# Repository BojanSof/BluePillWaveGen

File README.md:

# STM32 BluePill DDS WaveGen

DDS function generator implemented with STM32 BluePill board, based on
STM32F103C8T6 microcontroller, 8-bit R-2R ladder DAC and additional circuitry
for removing the DC offset.

The user interface is realized with OLED display based on SSD1306 controller and
incremental rotary encoder.

## Specs

Goal specs:

- Waveforms: sine, square, triangle, sawtooth (arbitrary waveforms can easily be
  added)
- Frequency: 0 - 35 kHz, frequncy resolution is variable
- Amplitude: 500 - 3000 mV (software control)

Additional tests and modifications should be done to reach the specs.

## Working Principle

The MCU generates the data for the 8-bit R-2R ladder D/A converter.

Two of the op amps inside TL084 are used as voltage buffers, one for the output
of the DAC and the second one for the variable voltage generated by filtering
PWM signal outputed by the MCU.
This variable voltage is used to remove the DC offset of the generated waveform.
Removing the DC offset is realised with the third op amp, which subtracts the
output of the DAC and the variable voltage and multiplies this difference by
1.82 so the output signal has maximum amplitude of 3 V.

To generate the data for the DAC, each waveform has lookup table stored in the
Flash memory of the MCU, with 256 elements with size 1 byte.
The values stored in the table are actually the data that need to be fed into
the DAC.
During runtime, whole or part of the table is copied into SRAM of the MCU, based
on the frequency of the waveform.
By changing the LUT, arbitrary periodic waveforms can be generated.

Timer 2 of the MCU is configured to generate DMA request.
It has base clock of  14.4 MHz and the value stored in the Auto-Reload Register 
(ARR) depends on the  frequency of the waveform. The value for ARR is calculated
using the following formula:

<center>ARR=TIM2\_BaseClock/(L\*f) - 1</center>

where L is the size of the LUT stored in SRAM and f is the frequency of the
waveform.

The DMA unit transfers data from the LUT in SRAM to the GPIOA output data
register.
The pins PA0-PA7 are used to output the data to the DAC.
Because the output data register of GPIOA is used, the pins PA8-PA15 can not be
used as general purpose outputs, but can be used in the other modes.
This problem can be resolved by writing to the bit set reset register instead of
the output data register.

## Software

The software was written in C, using STM32 HAL library, in STM32CubeIDE.

I have also written SSD1306 driver which can be further developed to include
more functionalities.

The code also includes isntantenous rotational speed measurement for the rotary
encoder with goal to change the values for frequency and amplitude based on the
rotational speed, i.e. faster turning of the encoder results in greater change
of the value.
This part of the code should also be improved, for better user experience.

## Experimental results

The following waveforms are measured with DSO150 oscilloscope.

<table>
  <tr>
    <td> </td>
    <td> </td>
    <td> </td>
    <td> </td>
    <td> </td>
  </tr> 
  <tr>
    <td> </td>
    <td> </td>
    <td> </td>
    <td> </td>
    <td> </td>
  </tr> 
  <tr>
    <td> </td>
    <td> </td>
    <td> </td>
    <td> </td>
    <td> </td>
  </tr> 
</table>

## Further improvements

- Additional tests and calibration to conclude the frequency and amplitude resolution
- USB virtual serial port to transfer LUT data for arbitrary waveform
- Low-pass filter after DAC output

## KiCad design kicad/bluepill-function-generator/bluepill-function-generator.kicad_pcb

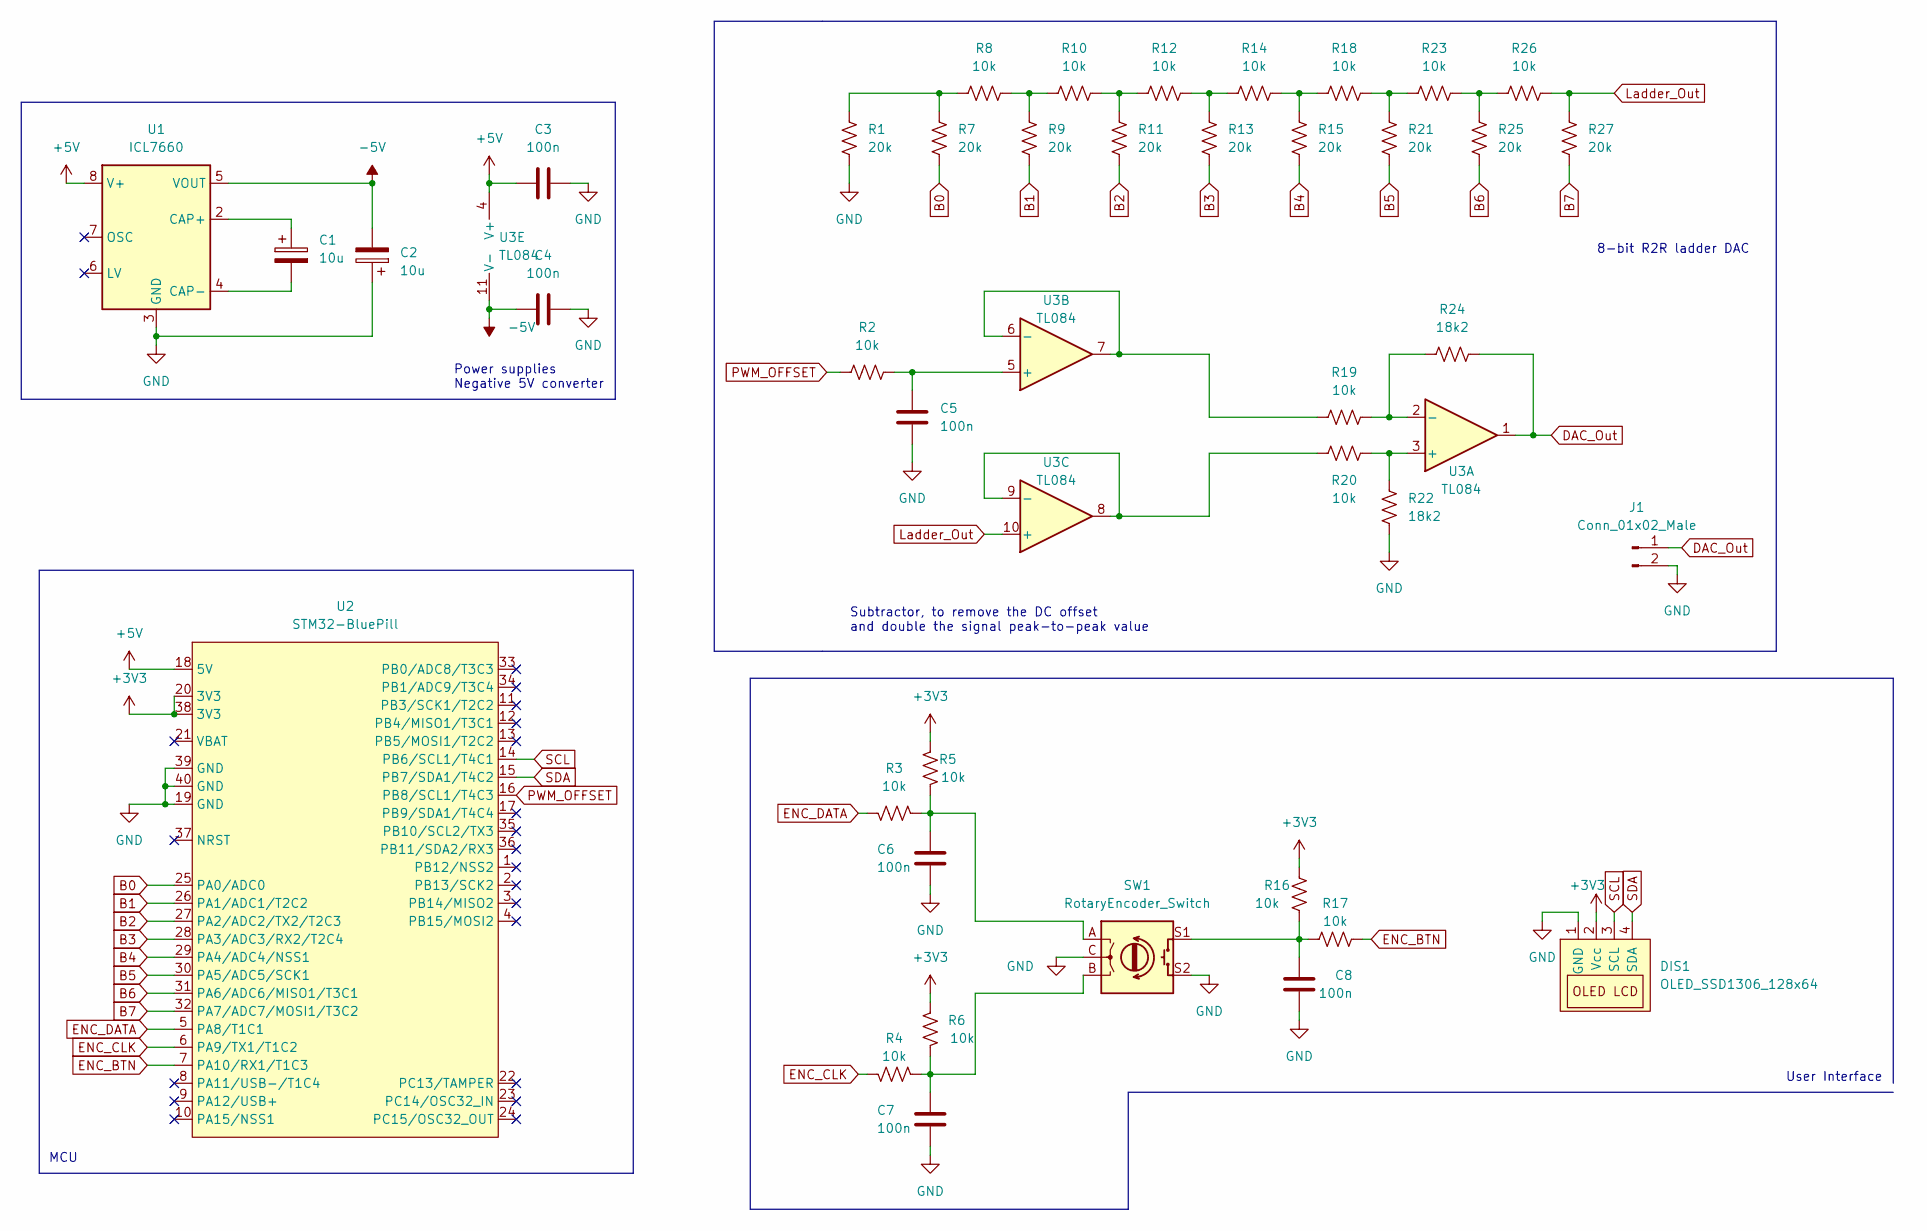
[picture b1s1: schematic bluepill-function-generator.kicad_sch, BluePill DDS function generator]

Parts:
C1, C2: 10u; CP_Radial_D5.0mm_P2.50mm
C3, C4, C5, C6, C7, C8: 100n; C_Disc_D5.0mm_W2.5mm_P5.00mm
DIS1: OLED_SSD1306_128x64; OLED-SSD1306-128x64
J1: Conn_01x02_Male; PinHeader_1x02_P2.54mm_Vertical
R1, R7, R9, R11, R13, R15, R21, R25, R27: 20k; R_Axial_DIN0207_L6.3mm_D2.5mm_P7.62mm_Horizontal
R2, R3, R4, R5, R6, R8, R10, R12, R14, R16, R17, R18, R19, R20, R23, R26: 10k; R_Axial_DIN0207_L6.3mm_D2.5mm_P7.62mm_Horizontal
R22, R24: 18k2; R_Axial_DIN0207_L6.3mm_D2.5mm_P7.62mm_Horizontal
SW1: RotaryEncoder_Switch; RotaryEncoder_Alps_EC11E-Switch_Vertical_H20mm
U1: ICL7660; DIP-8_W7.62mm
U2: STM32-BluePill
U3: TL084; DIP-14_W7.62mm

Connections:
+3V3: DIS1.2 (Vcc), R5.2, R6.2, R16.2, U2.20 (3V3), U2.38 (3V3)
+5V: C3.1, U1.8 (V+), U2.18 (5V), U3.4 (V+)
-5V: C2.2, C4.1, U1.5 (VOUT), U3.11 (V-)
B0: R7.2, U2.25 (PA0/ADC0)
B1: R9.1, U2.26 (PA1/ADC1/T2C2)
B2: R11.2, U2.27 (PA2/ADC2/TX2/T2C3)
B3: R13.1, U2.28 (PA3/ADC3/RX2/T2C4)
B4: R15.2, U2.29 (PA4/ADC4/NSS1)
B5: R21.1, U2.30 (PA5/ADC5/SCK1)
B6: R25.2, U2.31 (PA6/ADC6/MISO1/T3C1)
B7: R27.2, U2.32 (PA7/ADC7/MOSI1/T3C2)
DAC_Out: J1.1, R24.1, U3.1
ENC_BTN: R17.1, U2.7 (PA10/RX1/T1C3)
ENC_CLK: R4.1, U2.6 (PA9/TX1/T1C2)
ENC_DATA: R3.2, U2.5 (PA8/T1C1)
GND: C2.1, C3.2, C4.2, C5.1, C6.2, C7.2, C8.2, DIS1.1 (GND), J1.2, R1.1, R22.2, SW1.C, SW1.S2, U1.3 (GND), U2.19 (GND), U2.39 (GND), U2.40 (GND)
Ladder_Out: R26.1, R27.1, U3.10 (+)
unnamed: C1.1, U1.2 (CAP+)
unnamed: C1.2, U1.4 (CAP-)
unnamed: C5.2, R2.2, U3.5 (+)
unnamed: C6.1, R3.1, R5.1, SW1.A
unnamed: C7.1, R4.2, R6.1, SW1.B
unnamed: C8.1, R16.1, R17.2, SW1.S1
unnamed: R1.2, R7.1, R8.2
unnamed: R10.1, R11.1, R12.2
unnamed: R8.1, R9.2, R10.2
unnamed: R12.1, R13.2, R14.2
unnamed: R14.1, R15.1, R18.2
unnamed: R18.1, R21.2, R23.2
unnamed: R19.1, R24.2, U3.2 (-)
unnamed: R19.2, U3.6 (-), U3.7
unnamed: R20.1, R22.1, U3.3 (+)
unnamed: R20.2, U3.8, U3.9 (-)
unnamed: R23.1, R25.1, R26.2
PWM_OFFSET: R2.1, U2.16 (PB8/SCL1/T4C3)
SCL: DIS1.3 (SCL), U2.14 (PB6/SCL1/T4C1)
SDA: DIS1.4 (SDA), U2.15 (PB7/SDA1/T4C2)

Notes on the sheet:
8-bit R2R ladder DAC
User Interface
MCU
Subtractor, to remove the DC offset and double the signal peak-to-peak value
Power supplies Negative 5V converter

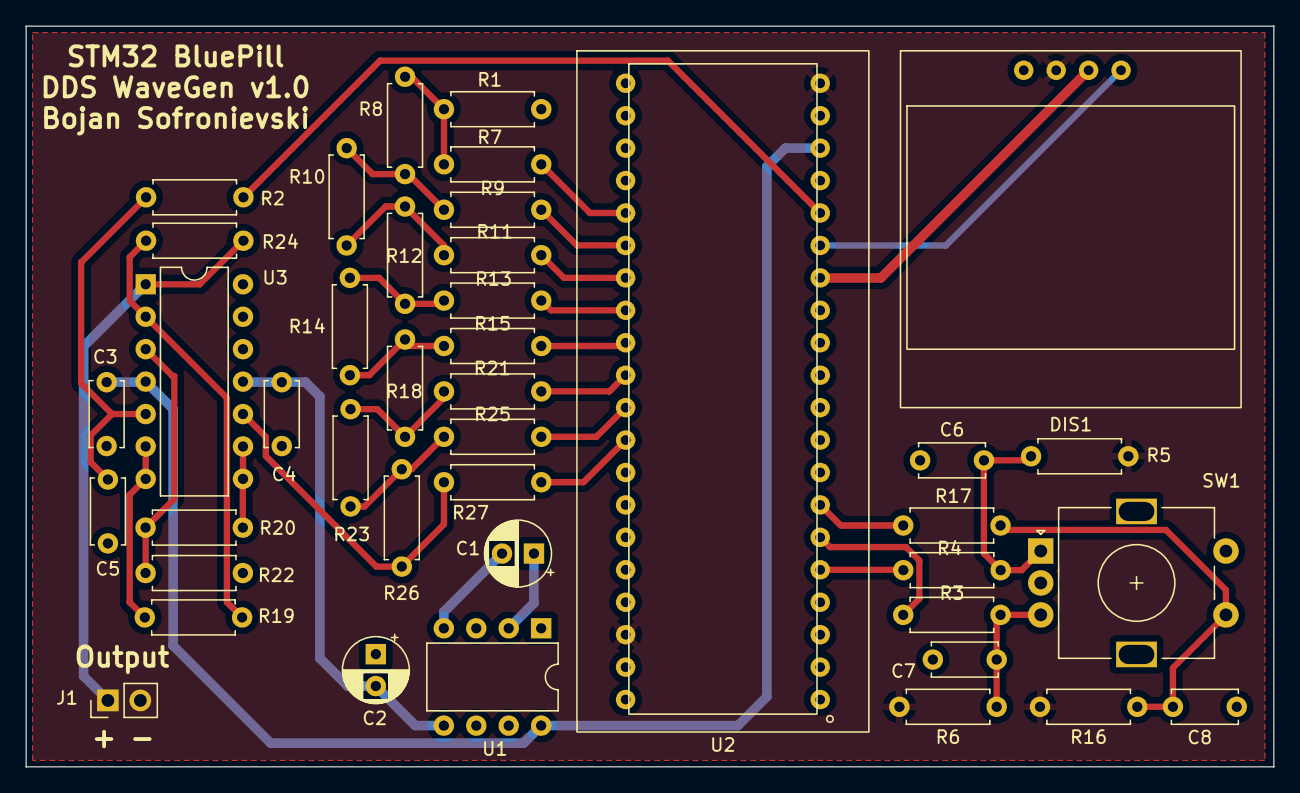
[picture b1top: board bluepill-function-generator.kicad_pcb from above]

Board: 2 copper layers, 97.7 x 58.0 mm, 41 parts (0 on the bottom side), 37 nets.

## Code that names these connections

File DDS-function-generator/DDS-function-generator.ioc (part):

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Mcu.Name=STM32F103C(8-B)Tx
Mcu.Package=LQFP48
Mcu.UserName=STM32F103C8Tx
PA0-WKUP.GPIOParameters=GPIO_Speed,GPIO_Label
PA0-WKUP.GPIO_Label=DAC0
PA0-WKUP.GPIO_Speed=GPIO_SPEED_FREQ_HIGH
PA0-WKUP.Signal=GPIO_Output
PA1.GPIOParameters=GPIO_Speed,GPIO_Label
PA1.GPIO_Label=DAC1
PA1.GPIO_Speed=GPIO_SPEED_FREQ_HIGH
PA1.Signal=GPIO_Output
PA10.GPIOParameters=GPIO_Label
PA10.GPIO_Label=ENC_BTN
PA10.Signal=GPIO_Input
PA13.Mode=Serial_Wire
PA13.Signal=SYS_JTMS-SWDIO
PA14.Mode=Serial_Wire
PA14.Signal=SYS_JTCK-SWCLK
PA2.GPIOParameters=GPIO_Speed,GPIO_Label
PA2.GPIO_Label=DAC2
PA2.GPIO_Speed=GPIO_SPEED_FREQ_HIGH
PA2.Signal=GPIO_Output
PA3.GPIOParameters=GPIO_Speed,GPIO_Label
PA3.GPIO_Label=DAC3
PA3.GPIO_Speed=GPIO_SPEED_FREQ_HIGH
PA3.Signal=GPIO_Output
PA4.GPIOParameters=GPIO_Speed,GPIO_Label
PA4.GPIO_Label=DAC4
PA4.GPIO_Speed=GPIO_SPEED_FREQ_HIGH
PA4.Signal=GPIO_Output
PA5.GPIOParameters=GPIO_Speed,GPIO_Label
PA5.GPIO_Label=DAC5
PA5.GPIO_Speed=GPIO_SPEED_FREQ_HIGH
PA5.Signal=GPIO_Output
PA6.GPIOParameters=GPIO_Speed,GPIO_Label
PA6.GPIO_Label=DAC6
PA6.GPIO_Speed=GPIO_SPEED_FREQ_HIGH
PA6.Signal=GPIO_Output
PA7.GPIOParameters=GPIO_Speed,GPIO_Label
PA7.GPIO_Label=DAC7
PA7.GPIO_Speed=GPIO_SPEED_FREQ_HIGH
PA7.Signal=GPIO_Output
PA8.Signal=S_TIM1_CH1
PA9.Signal=S_TIM1_CH2
PB0.Signal=GPIO_Output
PB1.Signal=GPIO_Output
PB6.Mode=I2C
PB6.Signal=I2C1_SCL
PB7.Mode=I2C
PB7.Signal=I2C1_SDA
PB8.Signal=S_TIM4_CH3
PD0-OSC_IN.Mode=HSE-External-Oscillator
PD0-OSC_IN.Signal=RCC_OSC_IN
PD1-OSC_OUT.Mode=HSE-External-Oscillator
PD1-OSC_OUT.Signal=RCC_OSC_OUT
RCC.SYSCLKFreq_VALUE=72000000
RCC.SYSCLKSource=RCC_SYSCLKSOURCE_PLLCLK
board=custom
